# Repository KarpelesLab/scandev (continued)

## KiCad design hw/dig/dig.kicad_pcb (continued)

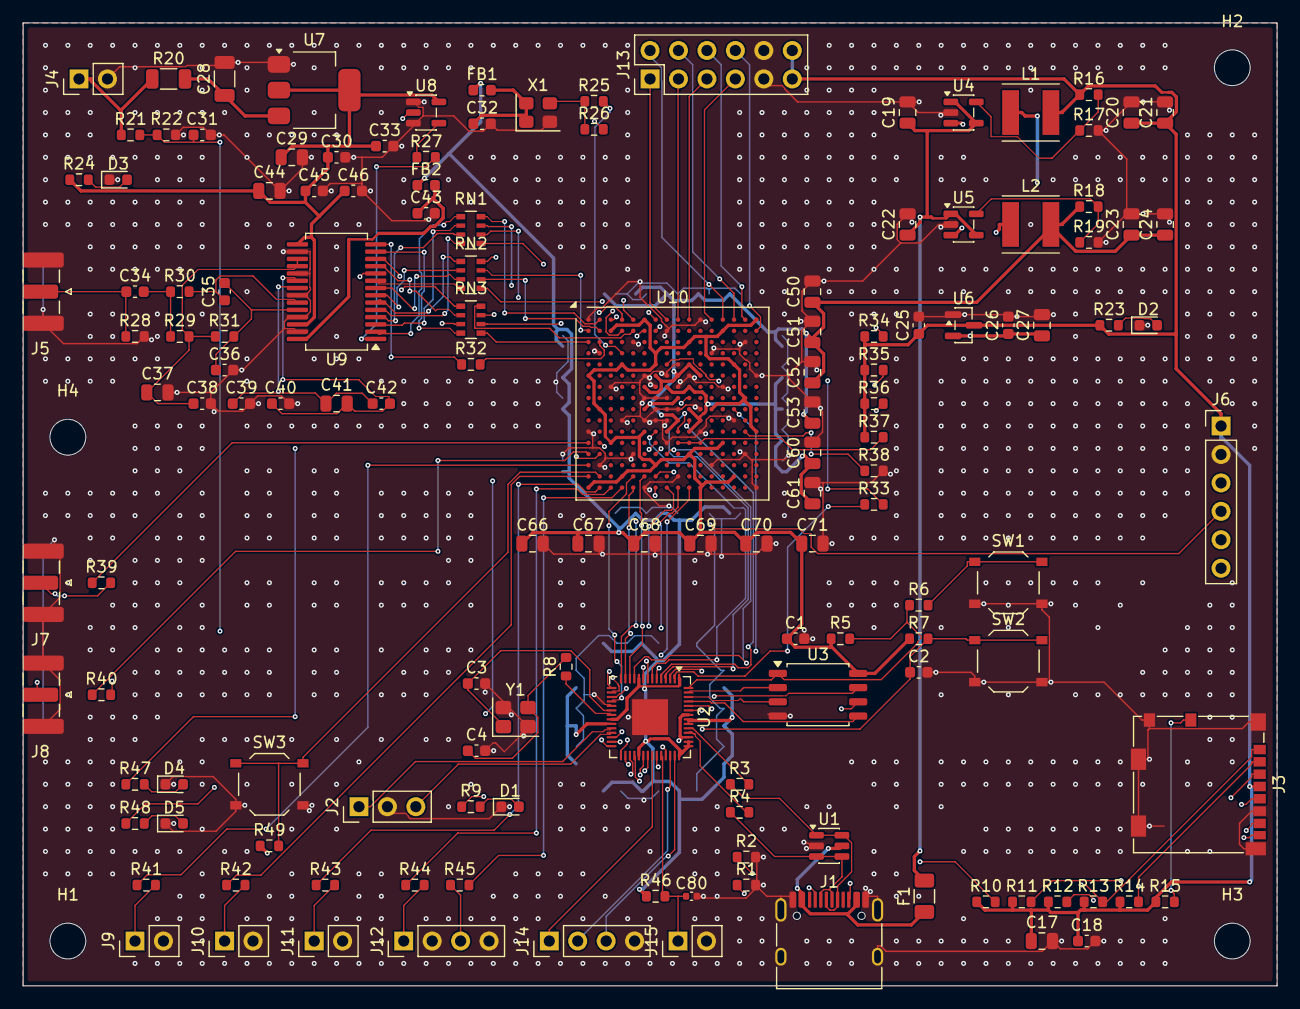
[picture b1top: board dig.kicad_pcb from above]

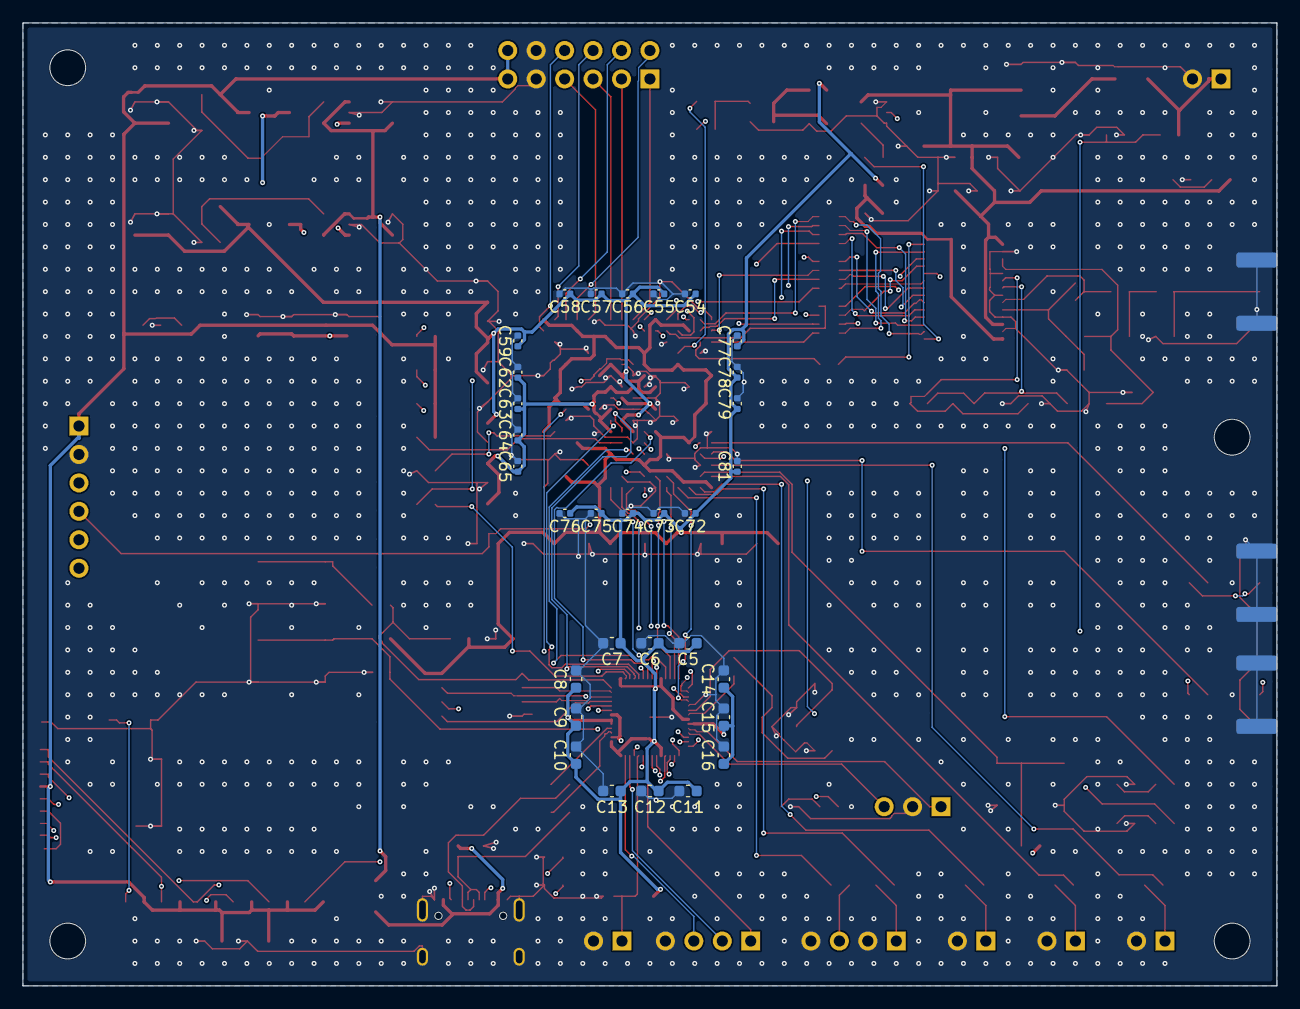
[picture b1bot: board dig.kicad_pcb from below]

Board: 4 copper layers, 112.0 x 86.0 mm, 174 parts (31 on the bottom side), 136 nets.

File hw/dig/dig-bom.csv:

Comment,Designator,Footprint,LCSC,MPN
100n,"C1,C10,C11,C12,C14,C15,C18,C2,C30,C31,C32,C33,C34,C36,C38,C39,C40,C42,C43,C45,C46,C5,C6,C7,C8,C9",C_0603_1608Metric,C14663,
1u,"C13,C16,C25,C26",C_0603_1608Metric,C15849,
10u,"C17,C19,C22,C27,C37,C41,C44",C_0805_2012Metric,C15850,
22u,"C20,C21,C23,C24,C29,C50,C51,C60,C66,C67",C_0805_2012Metric,C98190,
10u 25V,C28,C_1206_3216Metric,C9807,
15p,"C3,C4",C_0603_1608Metric,C107037,
22p,C35,C_0603_1608Metric,C525244,
4.7u,"C52,C53,C61,C68,C69,C70,C71",C_0805_2012Metric,C1779,
100n,"C54,C55,C56,C57,C58,C59,C62,C63,C64,C65,C72,C73,C74,C75,C76,C77,C78,C79,C80,C81",C_0402_1005Metric,C1525,
green,"D1,D2,D3,D4,D5",LED_0603_1608Metric,C72043,
1A hold,F1,Fuse_1206_3216Metric,C20800,SMD1206P100TF
600R,"FB1,FB2",L_0603_1608Metric,C1002,GZ1608D601TF
M3,"H1,H2,H3,H4",MountingHole_3.2mm_M3,,
USB-C,J1,USB_C_Receptacle_HRO_TYPE-C-31-M-12,C165948,TYPE-C-31-M-12
BLANK,J10,PinHeader_1x02_P2.54mm_Vertical,,
QDAMP,J11,PinHeader_1x02_P2.54mm_Vertical,,
TRIG,J12,PinHeader_1x04_P2.54mm_Vertical,,
PMOD,J13,PinHeader_2x06_P2.54mm_Vertical,,
EXP,J14,PinHeader_1x04_P2.54mm_Vertical,,
TEMP,J15,PinHeader_1x02_P2.54mm_Vertical,,
SWD,J2,PinHeader_1x03_P2.54mm_Vertical,,
microSD,J3,microSD_HC_Molex_104031-0811,C585350,104031-0811
12V IN,J4,PinHeader_1x02_P2.54mm_Vertical,,
RX IN,J5,SMA_Samtec_SMA-J-P-H-ST-EM1_EdgeMount,,
JTAG,J6,PinHeader_1x06_P2.54mm_Vertical,,
TX HI,J7,SMA_Samtec_SMA-J-P-H-ST-EM1_EdgeMount,,
TX LO,J8,SMA_Samtec_SMA-J-P-H-ST-EM1_EdgeMount,,
PA EN,J9,PinHeader_1x02_P2.54mm_Vertical,,
2.2u,"L1,L2",L_Changjiang_FNR5040S,C167957,FNR5040S2R2MT
5.1k,"R1,R2",R_0603_1608Metric,C2907044,
10k,"R10,R11,R12,R13,R14,R15,R46,R49,R5,R7",R_0603_1608Metric,C25804,
100k,"R16,R18,R21",R_0603_1608Metric,C115320,
22k,"R17,R22",R_0603_1608Metric,C114065,
150k,R19,R_0603_1608Metric,C402995,
10,R20,R_1206_3216Metric,C2828881,
1k,"R23,R29,R37,R38,R45,R47,R48,R6,R8,R9",R_0603_1608Metric,C21190,
2.2k,R24,R_0603_1608Metric,C844925,
33,"R25,R26,R27,R30,R31,R32,R33",R_0603_1608Metric,C23140,
49.9,"R28,R39,R40",R_0603_1608Metric,C23185,
27,"R3,R4",R_0603_1608Metric,C25190,
4.7k,"R34,R35,R36",R_0603_1608Metric,C116693,
100,"R41,R42,R43,R44",R_0603_1608Metric,C22775,
33,"RN1,RN2,RN3",R_Array_Convex_4x0603,C25508,4D03WGJ0330T5E
BOOTSEL,SW1,SW_Push_1P1T_XKB_TS-1187A,C318889,TS-1187A-C-C-B
RESET,SW2,SW_Push_1P1T_XKB_TS-1187A,C318889,TS-1187A-C-C-B
USER,SW3,SW_Push_1P1T_XKB_TS-1187A,C318889,TS-1187A-C-C-B
USBLC6-2SC6,U1,SOT-23-6,C7519,USBLC6-2SC6
XC7A35T-FTG256,U10,Xilinx_FTG256,C181716,XC7A35T-2FTG256C
RP2040,U2,QFN-56-1EP_7x7mm_P0.4mm_EP3.2x3.2mm,C2040,RP2040
W25Q16JV,U3,SOIC-8_5.3x5.3mm_P1.27mm,C131025,W25Q16JVSSIQ
TLV62569,"U4,U5",SOT-23-5,C141836,TLV62569DBVR
XC6206P182,U6,SOT-23,C51886219,XC6206P182MR
AMS1117-5.0,U7,SOT-223-3_TabPin2,C6187,AMS1117-5.0
74AHCT1G125,U8,SOT-23-5,C7484,SN74AHCT1G125DBVR
AD9226ARSZ,U9,SSOP-28_5.3x10.2mm_P0.65mm,C730053,AD9226ARSZ
50MHz,X1,Oscillator_SMD_Abracon_ASE-4Pin_3.2x2.5mm,C26267,SiT8008BI-22-33E-50.000000
12MHz,Y1,Crystal_SMD_3225-4Pin_3.2x2.5mm,C9002,X322512MSB4SI

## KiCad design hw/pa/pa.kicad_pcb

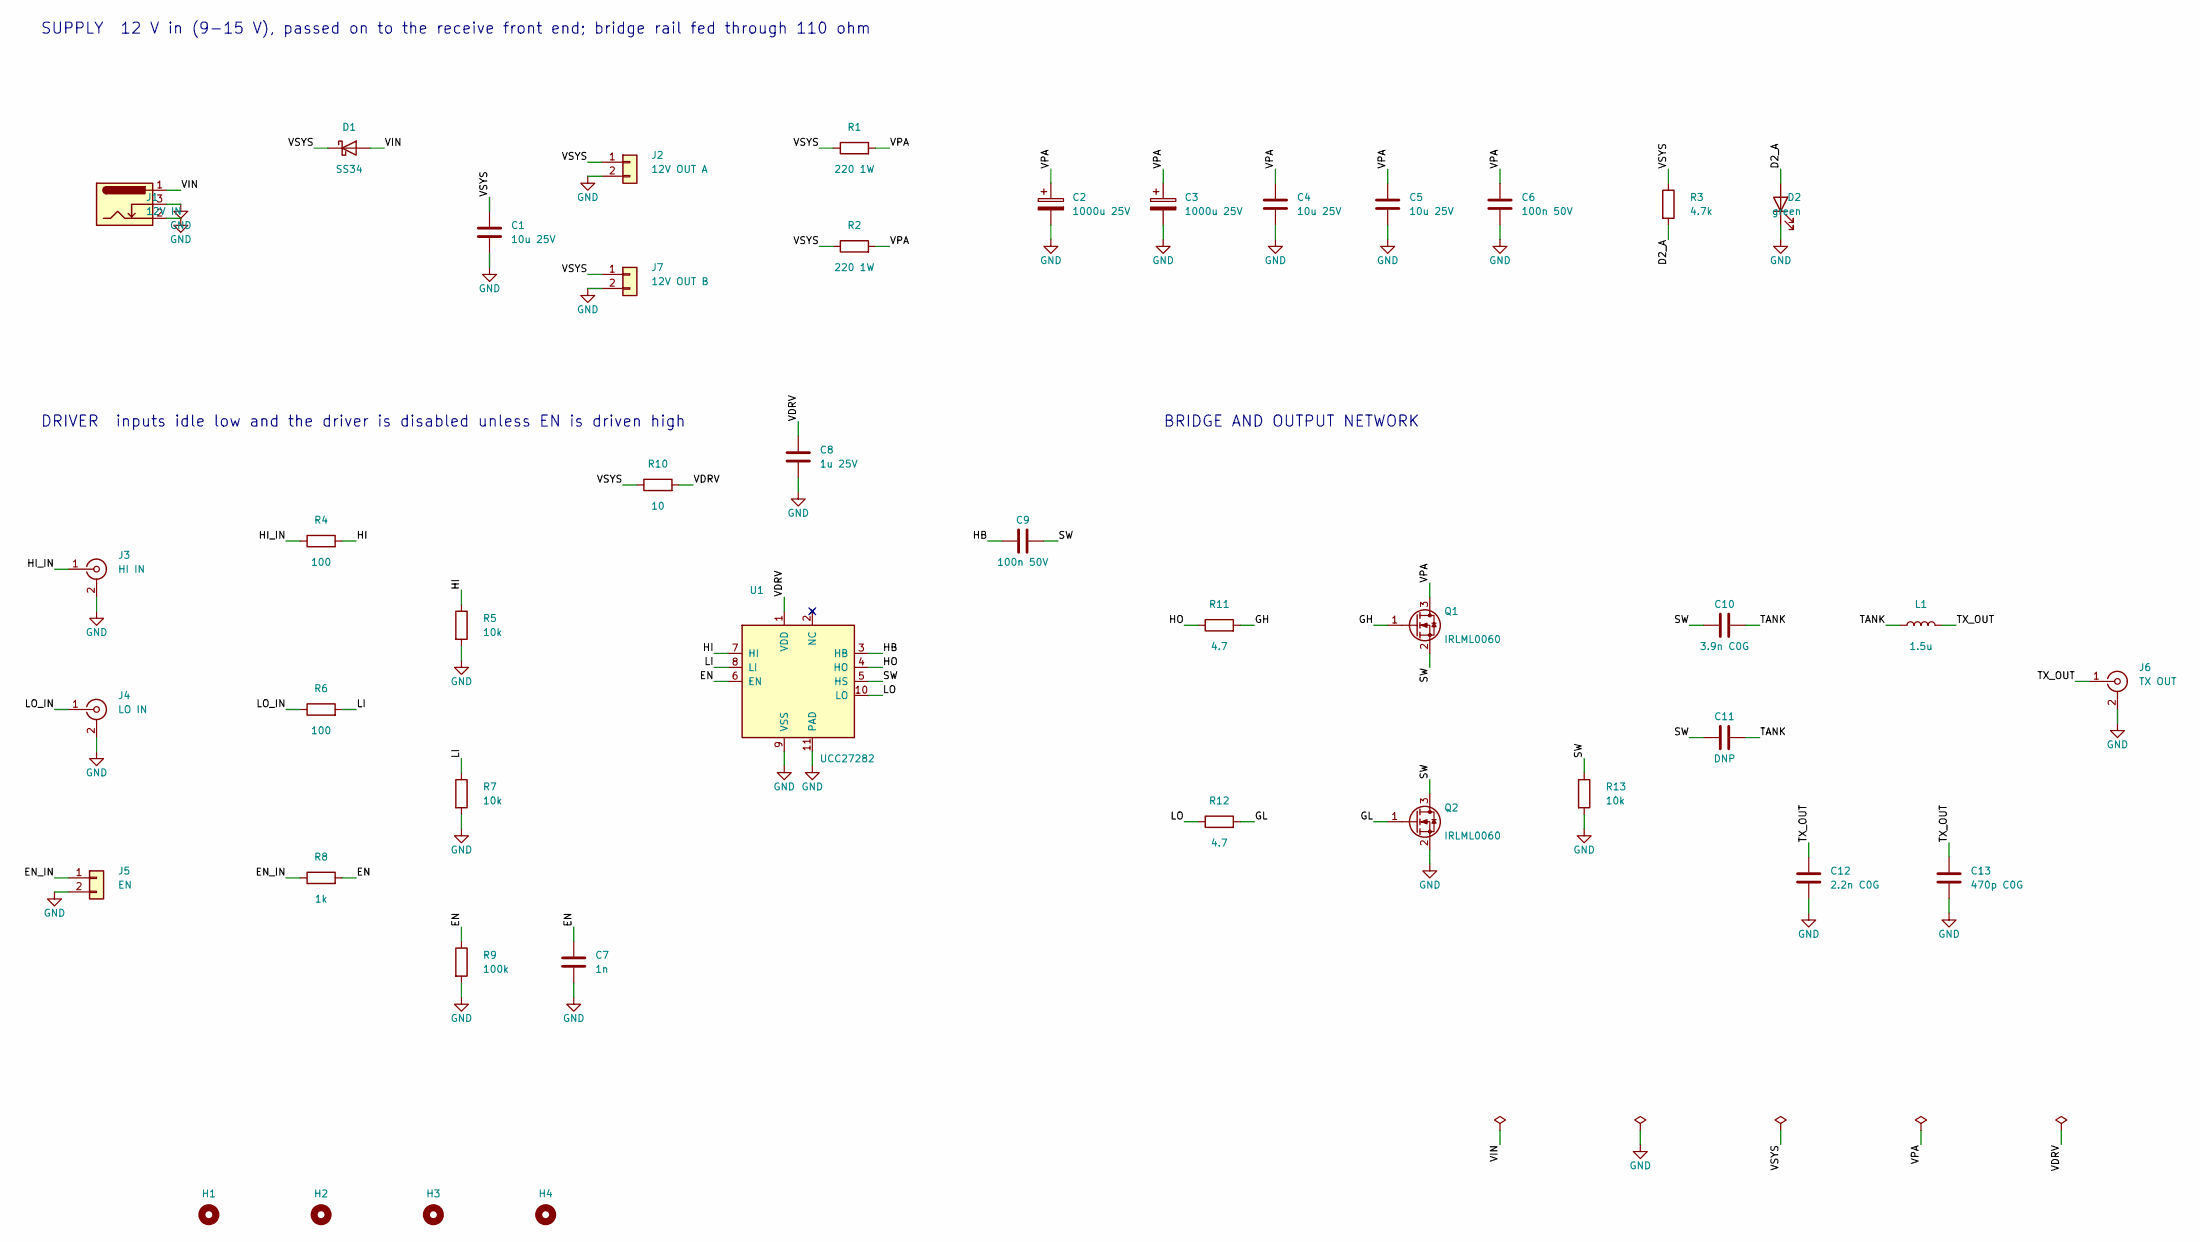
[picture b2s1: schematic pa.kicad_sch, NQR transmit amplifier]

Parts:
C1, C4, C5: 10u 25V; C_1206_3216Metric; LCSC C9807
C2, C3: 1000u 25V; CP_Radial_D10.0mm_P5.00mm; MPN 25YXJ1000M10X20; LCSC C88720
C6, C9: 100n 50V; C_0603_1608Metric; LCSC C88219
C7: 1n; C_0603_1608Metric; LCSC C106247
C8: 1u 25V; C_0603_1608Metric; LCSC C92848
C10: 3.9n C0G; C_0805_2012Metric; LCSC C97901
C11: DNP; C_0805_2012Metric
C12: 2.2n C0G; C_0805_2012Metric; LCSC C513663
C13: 470p C0G; C_0805_2012Metric; LCSC C575439
D1: SS34; D_SMA; MPN SS34; LCSC C8678
D2: green; LED_0603_1608Metric; LCSC C72043
H1, H2, H3, H4: M3; MountingHole_3.2mm_M3
J1: 12V IN; BarrelJack_Horizontal; MPN DC005-T; LCSC C431532
J2: 12V OUT A; PinHeader_1x02_P2.54mm_Vertical
J3: HI IN; SMA_Samtec_SMA-J-P-H-ST-EM1_EdgeMount
J4: LO IN; SMA_Samtec_SMA-J-P-H-ST-EM1_EdgeMount
J5: EN; PinHeader_1x02_P2.54mm_Vertical
J6: TX OUT; SMA_Samtec_SMA-J-P-H-ST-EM1_EdgeMount
J7: 12V OUT B; PinHeader_1x02_P2.54mm_Vertical
L1: 1.5u; L_Sunlord_MWSA0503S; MPN MWSA0503S-1R5MT; LCSC C408407
Q1, Q2: IRLML0060; SOT-23; MPN IRLML0060TRPBF; LCSC C5122025
R1, R2: 220 1W; R_2512_6332Metric; LCSC C38808
R3: 4.7k; R_0603_1608Metric; LCSC C116693
R4, R6: 100; R_0603_1608Metric; LCSC C22775
R5, R7, R13: 10k; R_0603_1608Metric; LCSC C25804
R8: 1k; R_0603_1608Metric; LCSC C21190
R9: 100k; R_0603_1608Metric; LCSC C115320
R10: 10; R_0603_1608Metric; LCSC C22859
R11, R12: 4.7; R_0603_1608Metric; LCSC C844794
U1: UCC27282; Texas_DRC0010J; MPN UCC27282DRCR; LCSC C2677035

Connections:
D2_A: D2.2 (A), R3.2
EN: C7.1, R8.2, R9.1, U1.6 (EN)
EN_IN: J5.1, R8.1
GH: Q1.1 (G), R11.2
GL: Q2.1 (G), R12.2
GND: C1.2, C2.2, C3.2, C4.2, C5.2, C6.2, C7.2, C8.2, C12.2, C13.2, D2.1 (K), J1.2, J1.3, J2.2, J3.2 (Ext), J4.2 (Ext), J5.2, J6.2 (Ext), J7.2, Q2.2 (S), R5.2, R7.2, R9.2, R13.2, U1.9 (VSS), U1.11 (PAD)
HB: C9.1, U1.3 (HB)
HI: R4.2, R5.1, U1.7 (HI)
HI_IN: J3.1 (In), R4.1
HO: R11.1, U1.4 (HO)
LI: R6.2, R7.1, U1.8 (LI)
LO: R12.1, U1.10 (LO)
LO_IN: J4.1 (In), R6.1
SW: C9.2, C10.1, C11.1, Q1.2 (S), Q2.3 (D), R13.1, U1.5 (HS)
TANK: C10.2, C11.2, L1.1
TX_OUT: C12.1, C13.1, J6.1 (In), L1.2
VDRV: C8.1, R10.2, U1.1 (VDD)
VIN: D1.2 (A), J1.1
VPA: C2.1, C3.1, C4.1, C5.1, C6.1, Q1.3 (D), R1.2, R2.2
VSYS: C1.1, D1.1 (K), J2.1, J7.1, R1.1, R2.1, R3.1, R10.1

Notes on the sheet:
SUPPLY 12 V in (9-15 V), passed on to the receive front end; bridge rail fed through 110 ohm
DRIVER inputs idle low and the driver is disabled unless EN is driven high
BRIDGE AND OUTPUT NETWORK

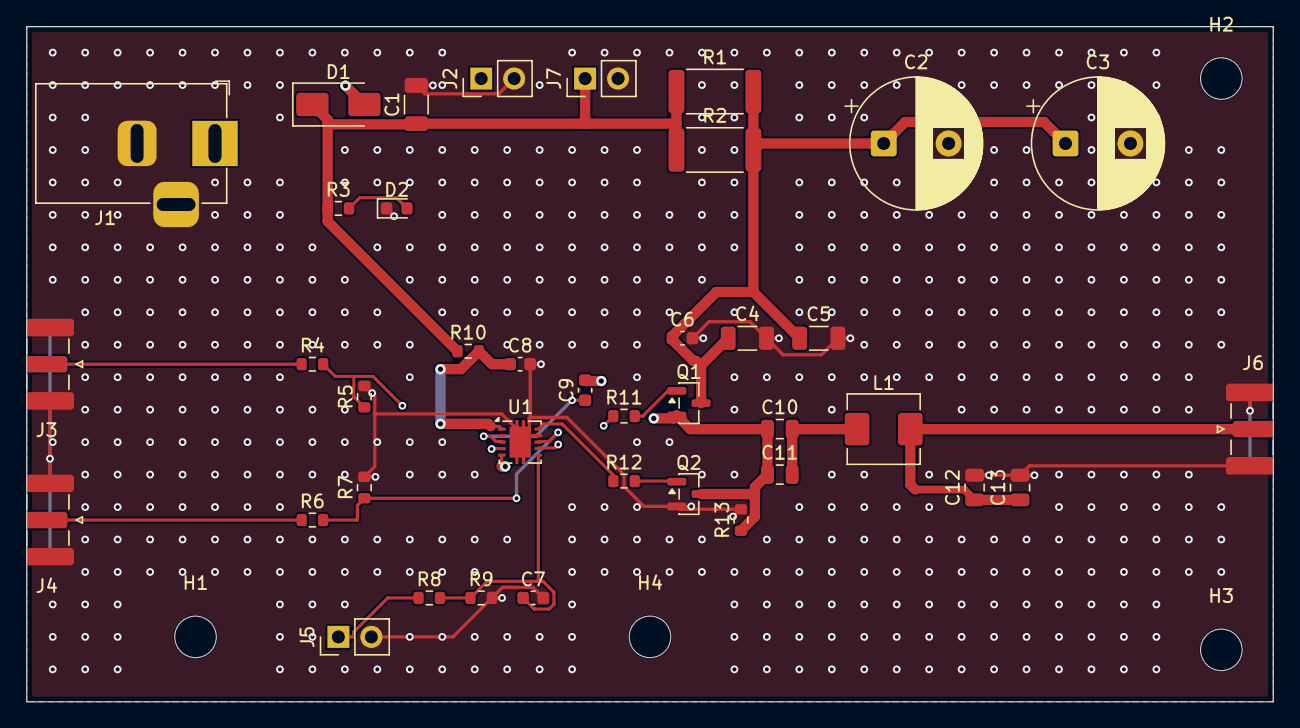
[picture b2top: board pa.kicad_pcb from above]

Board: 4 copper layers, 96.0 x 52.0 mm, 43 parts (0 on the bottom side), 20 nets.

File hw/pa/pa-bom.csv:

Comment,Designator,Footprint,LCSC,MPN
10u 25V,"C1,C4,C5",C_1206_3216Metric,C9807,
3.9n C0G,C10,C_0805_2012Metric,C97901,
DNP,C11,C_0805_2012Metric,,
2.2n C0G,C12,C_0805_2012Metric,C513663,
470p C0G,C13,C_0805_2012Metric,C575439,
1000u 25V,"C2,C3",CP_Radial_D10.0mm_P5.00mm,C88720,25YXJ1000M10X20
100n 50V,"C6,C9",C_0603_1608Metric,C88219,
1n,C7,C_0603_1608Metric,C106247,
1u 25V,C8,C_0603_1608Metric,C92848,
SS34,D1,D_SMA,C8678,SS34
green,D2,LED_0603_1608Metric,C72043,
M3,"H1,H2,H3,H4",MountingHole_3.2mm_M3,,
12V IN,J1,BarrelJack_Horizontal,C431532,DC005-T
12V OUT A,J2,PinHeader_1x02_P2.54mm_Vertical,,
HI IN,J3,SMA_Samtec_SMA-J-P-H-ST-EM1_EdgeMount,,
LO IN,J4,SMA_Samtec_SMA-J-P-H-ST-EM1_EdgeMount,,
EN,J5,PinHeader_1x02_P2.54mm_Vertical,,
TX OUT,J6,SMA_Samtec_SMA-J-P-H-ST-EM1_EdgeMount,,
12V OUT B,J7,PinHeader_1x02_P2.54mm_Vertical,,
1.5u,L1,L_Sunlord_MWSA0503S,C408407,MWSA0503S-1R5MT
IRLML0060,"Q1,Q2",SOT-23,C5122025,IRLML0060TRPBF
220 1W,"R1,R2",R_2512_6332Metric,C38808,
10,R10,R_0603_1608Metric,C22859,
4.7,"R11,R12",R_0603_1608Metric,C844794,
10k,"R13,R5,R7",R_0603_1608Metric,C25804,
4.7k,R3,R_0603_1608Metric,C116693,
100,"R4,R6",R_0603_1608Metric,C22775,
1k,R8,R_0603_1608Metric,C21190,
100k,R9,R_0603_1608Metric,C115320,
UCC27282,U1,Texas_DRC0010J,C2677035,UCC27282DRCR

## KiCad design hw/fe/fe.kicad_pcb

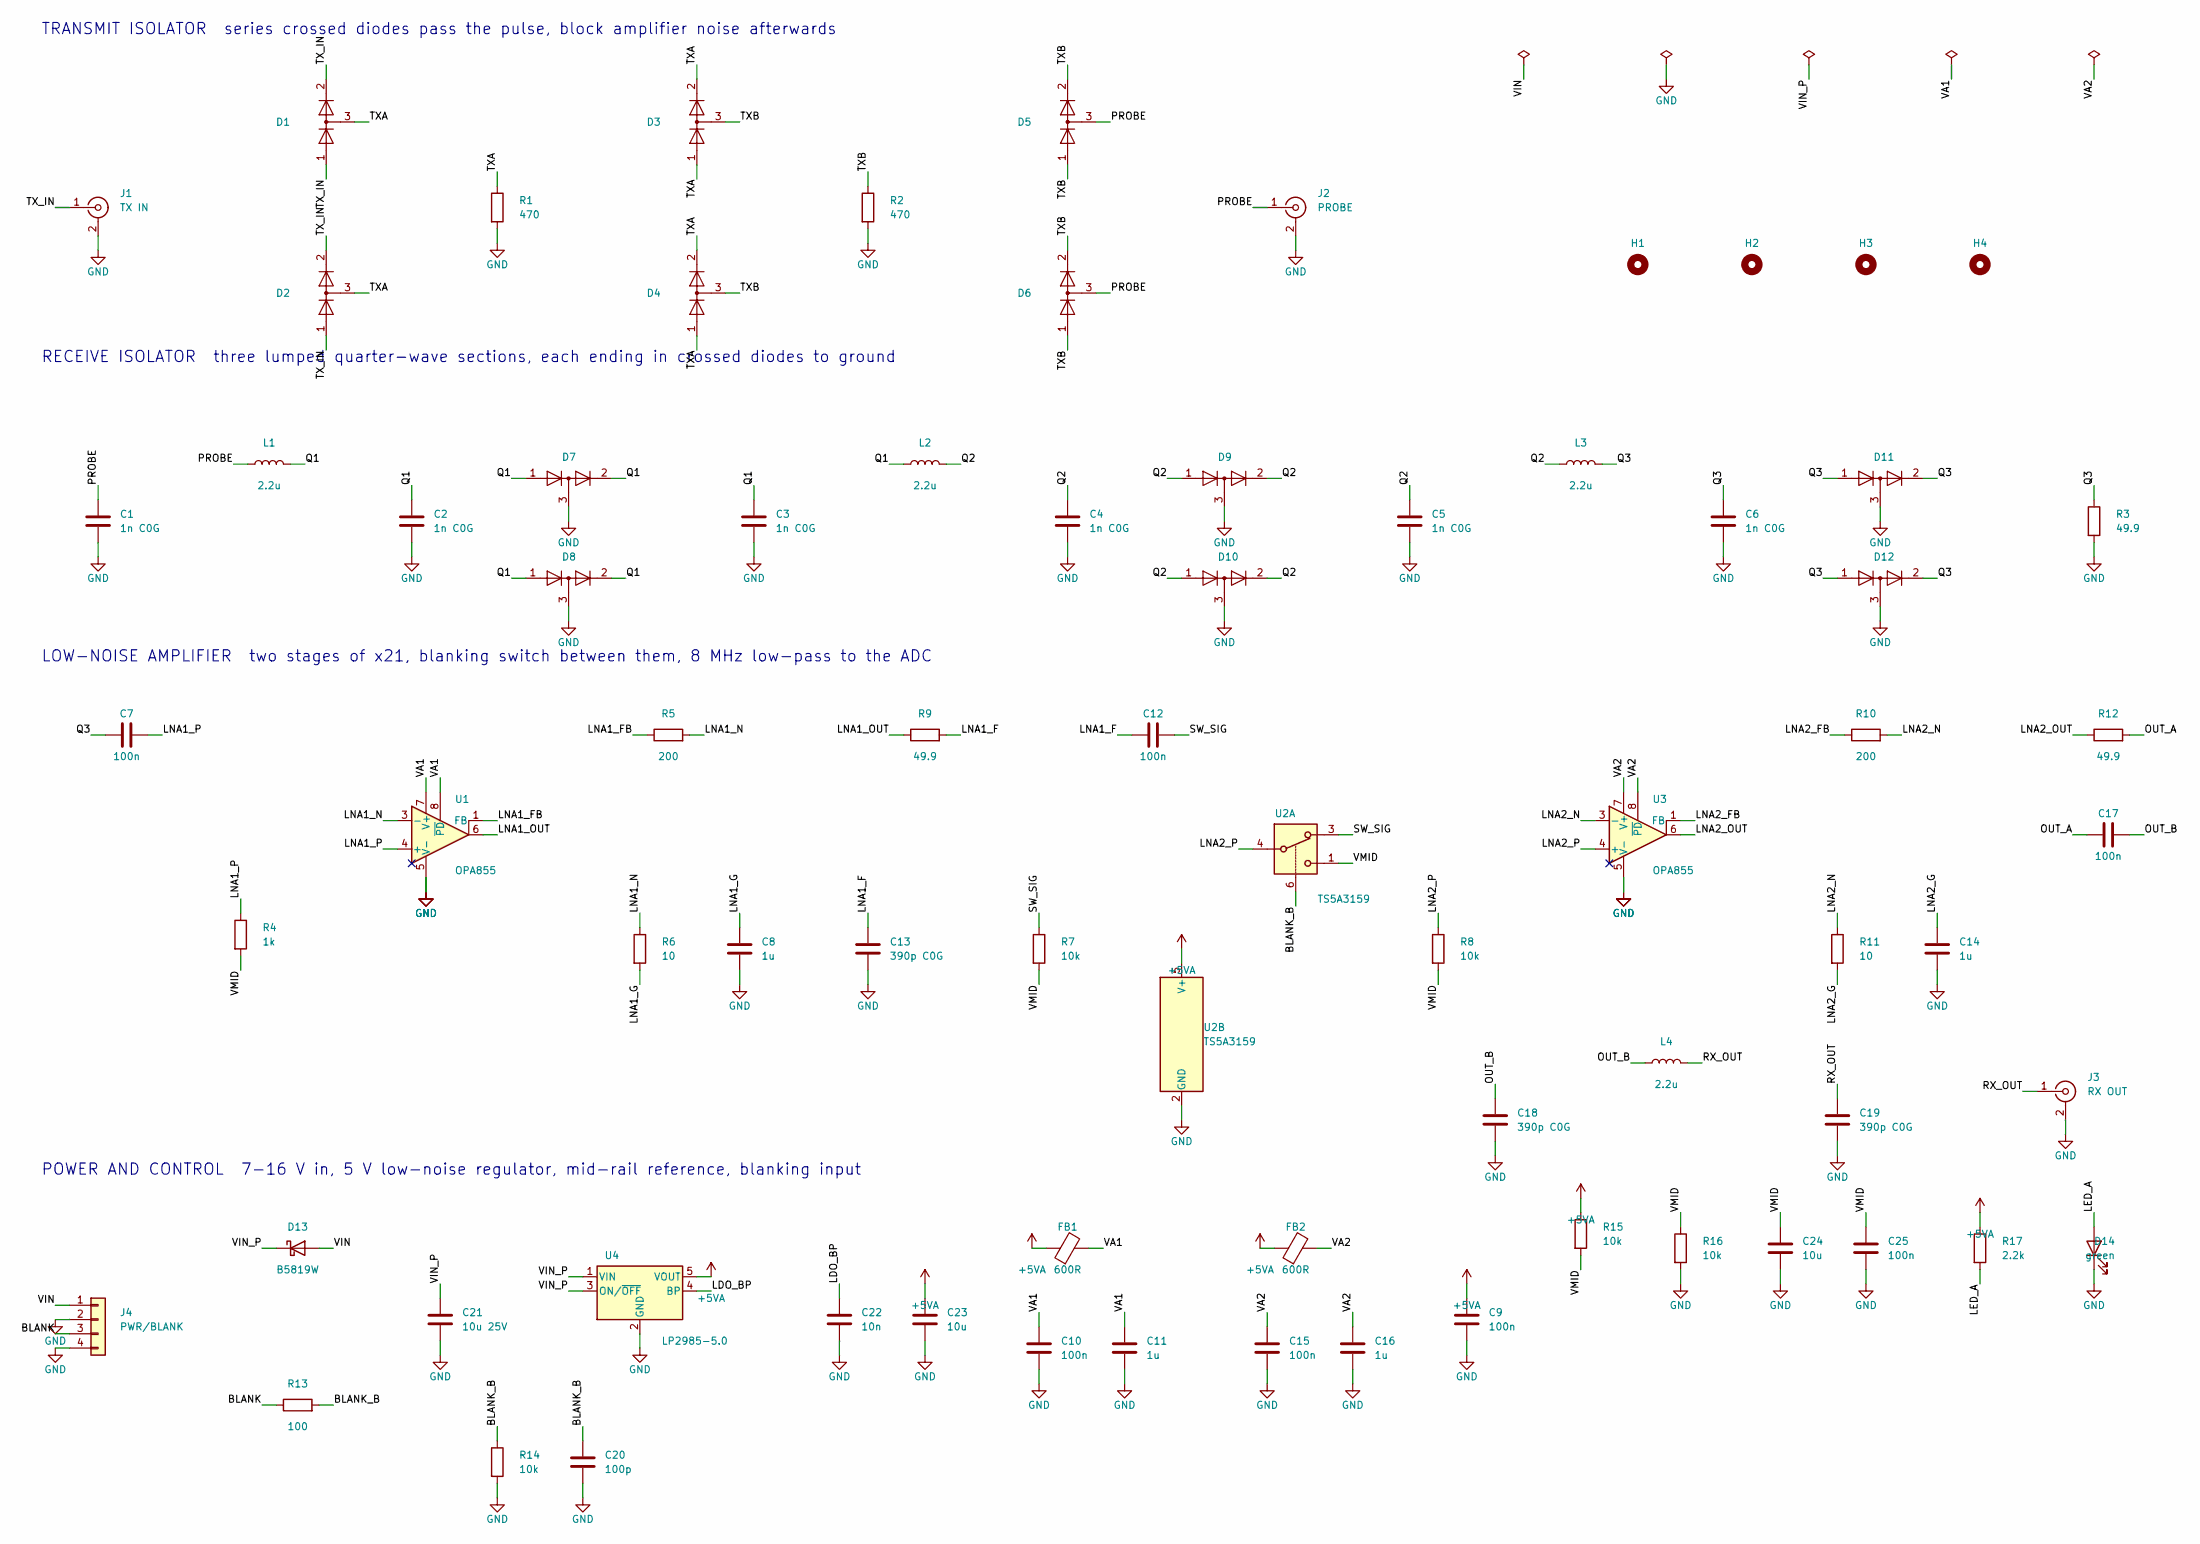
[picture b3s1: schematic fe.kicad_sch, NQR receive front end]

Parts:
C1, C2, C3, C4, C5, C6: 1n C0G; C_0805_2012Metric; LCSC C62774
C7, C9, C10, C12, C15, C17, C25: 100n; C_0603_1608Metric; LCSC C14663
C8, C11, C14, C16: 1u; C_0603_1608Metric; LCSC C15849
C13, C18, C19: 390p C0G; C_0603_1608Metric; LCSC C1667
C20: 100p; C_0603_1608Metric; LCSC C14858
C21: 10u 25V; C_0805_2012Metric; LCSC C84416
C22: 10n; C_0603_1608Metric; LCSC C57112
C23, C24: 10u; C_0805_2012Metric; LCSC C15850
D1, D2, D3, D4, D5, D6, D7, D8, D9, D10, D11, D12: BAV99; SOT-23; MPN BAV99LT1G; LCSC C82480
D13: B5819W; D_SOD-123; MPN B5819W; LCSC C8598
D14: green; LED_0603_1608Metric; LCSC C72043
FB1, FB2: 600R; L_0603_1608Metric; MPN GZ1608D601TF; LCSC C1002
H1, H2, H3, H4: M3; MountingHole_3.2mm_M3
J1: TX IN; SMA_Samtec_SMA-J-P-H-ST-EM1_EdgeMount
J2: PROBE; SMA_Samtec_SMA-J-P-H-ST-EM1_EdgeMount
J3: RX OUT; SMA_Samtec_SMA-J-P-H-ST-EM1_EdgeMount
J4: PWR/BLANK; PinHeader_1x04_P2.54mm_Vertical
L1, L2, L3, L4: 2.2u; L_Changjiang_FNR5040S; MPN FNR5040S2R2MT; LCSC C167957
R1, R2: 470; R_1206_3216Metric; LCSC C4502
R3, R9, R12: 49.9; R_0603_1608Metric; LCSC C23185
R4: 1k; R_0603_1608Metric; LCSC C21190
R5, R10: 200; R_0603_1608Metric; LCSC C8218
R6, R11: 10; R_0603_1608Metric; LCSC C22859
R7, R8, R14, R15, R16: 10k; R_0603_1608Metric; LCSC C25804
R13: 100; R_0603_1608Metric; LCSC C22775
R17: 2.2k; R_0603_1608Metric; LCSC C844925
U1, U3: OPA855; Texas_DSG0008A_WSON-8-1EP_2x2mm_P0.5mm_EP0.9x1.6mm; MPN OPA855IDSGR; LCSC C1409030
U2: TS5A3159; SOT-363_SC-70-6; MPN TS5A3159DCKR; LCSC C46388
U4: LP2985-5.0; SOT-23-5; MPN LP2985-50DBVR; LCSC C74511

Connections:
+5VA: C9.1, C23.1, FB1.1, FB2.1, R15.1, R17.1, U2.5 (V+), U4.5 (VOUT)
BLANK: J4.3, R13.1
BLANK_B: C20.1, R13.2, R14.1, U2.6
GND: C1.2, C2.2, C3.2, C4.2, C5.2, C6.2, C8.2, C9.2, C10.2, C11.2, C13.2, C14.2, C15.2, C16.2, C18.2, C19.2, C20.2, C21.2, C22.2, C23.2, C24.2, C25.2, D7.3 (K), D8.3 (K), D9.3 (K), D10.3 (K), D11.3 (K), D12.3 (K), D14.1 (K), J1.2 (Ext), J2.2 (Ext), J3.2 (Ext), J4.2, J4.4, R1.2, R2.2, R3.2, R14.2, R16.2, U1.5 (V-), U1.9 (V-), U2.2 (GND), U3.5 (V-), U3.9 (V-), U4.2 (GND)
LDO_BP: C22.1, U4.4 (BP)
LED_A: D14.2 (A), R17.2
LNA1_F: C12.1, C13.1, R9.2
LNA1_FB: R5.1, U1.1 (FB)
LNA1_G: C8.1, R6.2
LNA1_N: R5.2, R6.1, U1.3 (-)
LNA1_OUT: R9.1, U1.6
LNA1_P: C7.2, R4.1, U1.4 (+)
LNA2_FB: R10.1, U3.1 (FB)
LNA2_G: C14.1, R11.2
LNA2_N: R10.2, R11.1, U3.3 (-)
LNA2_OUT: R12.1, U3.6
LNA2_P: R8.1, U2.4, U3.4 (+)
OUT_A: C17.1, R12.2
OUT_B: C17.2, C18.1, L4.1
PROBE: C1.1, D5.3 (K), D6.3 (K), J2.1 (In), L1.1
Q1: C2.1, C3.1, D7.1 (K), D7.2 (A), D8.1 (K), D8.2 (A), L1.2, L2.1
Q2: C4.1, C5.1, D9.1 (K), D9.2 (A), D10.1 (K), D10.2 (A), L2.2, L3.1
Q3: C6.1, C7.1, D11.1 (K), D11.2 (A), D12.1 (K), D12.2 (A), L3.2, R3.1
RX_OUT: C19.1, J3.1 (In), L4.2
SW_SIG: C12.2, R7.1, U2.3
TXA: D1.3 (K), D2.3 (K), D3.1 (K), D3.2 (A), D4.1 (K), D4.2 (A), R1.1
TXB: D3.3 (K), D4.3 (K), D5.1 (K), D5.2 (A), D6.1 (K), D6.2 (A), R2.1
TX_IN: D1.1 (K), D1.2 (A), D2.1 (K), D2.2 (A), J1.1 (In)
VA1: C10.1, C11.1, FB1.2, U1.7 (V+), U1.8 (~PD)
VA2: C15.1, C16.1, FB2.2, U3.7 (V+), U3.8 (~PD)
VIN: D13.2 (A), J4.1
VIN_P: C21.1, D13.1 (K), U4.1 (VIN), U4.3 (ON/~OFF)
VMID: C24.1, C25.1, R4.2, R7.2, R8.2, R15.2, R16.1, U2.1

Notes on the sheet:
TRANSMIT ISOLATOR series crossed diodes pass the pulse, block amplifier noise afterwards
RECEIVE ISOLATOR three lumped quarter-wave sections, each ending in crossed diodes to ground
LOW-NOISE AMPLIFIER two stages of x21, blanking switch between them, 8 MHz low-pass to the ADC
POWER AND CONTROL 7-16 V in, 5 V low-noise regulator, mid-rail reference, blanking input

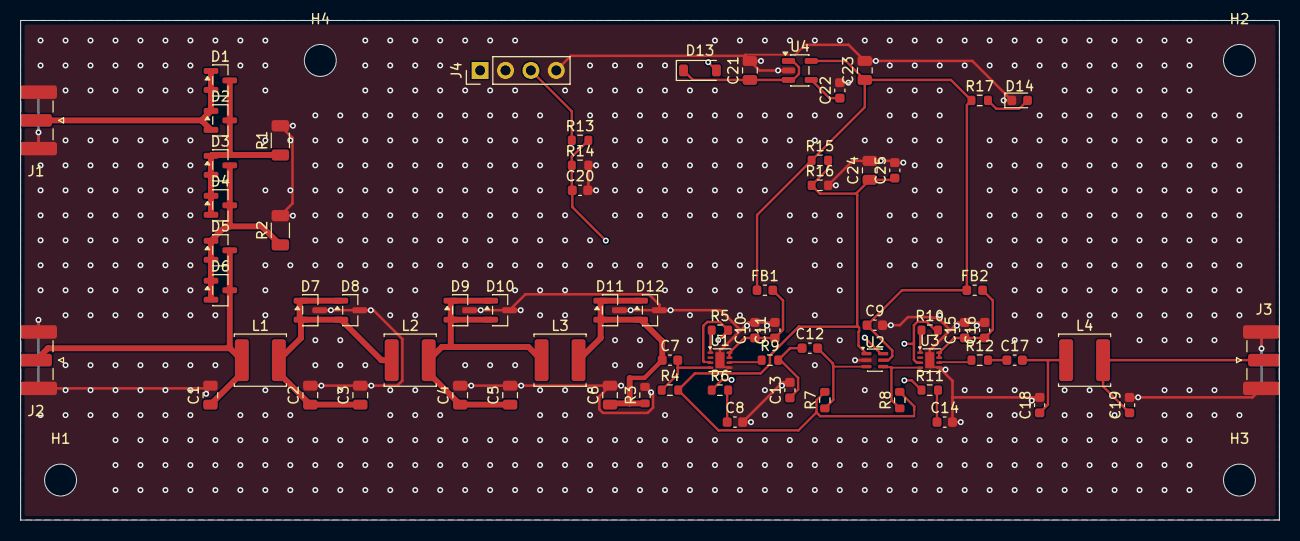
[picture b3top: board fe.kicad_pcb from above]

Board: 4 copper layers, 126.0 x 50.0 mm, 74 parts (0 on the bottom side), 33 nets.

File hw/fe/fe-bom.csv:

Comment,Designator,Footprint,LCSC,MPN
1n C0G,"C1,C2,C3,C4,C5,C6",C_0805_2012Metric,C62774,
100n,"C10,C12,C15,C17,C25,C7,C9",C_0603_1608Metric,C14663,
1u,"C11,C14,C16,C8",C_0603_1608Metric,C15849,
390p C0G,"C13,C18,C19",C_0603_1608Metric,C1667,
100p,C20,C_0603_1608Metric,C14858,
10u 25V,C21,C_0805_2012Metric,C84416,
10n,C22,C_0603_1608Metric,C57112,
10u,"C23,C24",C_0805_2012Metric,C15850,
BAV99,"D1,D10,D11,D12,D2,D3,D4,D5,D6,D7,D8,D9",SOT-23,C82480,BAV99LT1G
B5819W,D13,D_SOD-123,C8598,B5819W
green,D14,LED_0603_1608Metric,C72043,
600R,"FB1,FB2",L_0603_1608Metric,C1002,GZ1608D601TF
M3,"H1,H2,H3,H4",MountingHole_3.2mm_M3,,
TX IN,J1,SMA_Samtec_SMA-J-P-H-ST-EM1_EdgeMount,,
PROBE,J2,SMA_Samtec_SMA-J-P-H-ST-EM1_EdgeMount,,
RX OUT,J3,SMA_Samtec_SMA-J-P-H-ST-EM1_EdgeMount,,
PWR/BLANK,J4,PinHeader_1x04_P2.54mm_Vertical,,
2.2u,"L1,L2,L3,L4",L_Changjiang_FNR5040S,C167957,FNR5040S2R2MT
470,"R1,R2",R_1206_3216Metric,C4502,
200,"R10,R5",R_0603_1608Metric,C8218,
10,"R11,R6",R_0603_1608Metric,C22859,
49.9,"R12,R3,R9",R_0603_1608Metric,C23185,
100,R13,R_0603_1608Metric,C22775,
10k,"R14,R15,R16,R7,R8",R_0603_1608Metric,C25804,
2.2k,R17,R_0603_1608Metric,C844925,
1k,R4,R_0603_1608Metric,C21190,
OPA855,"U1,U3",Texas_DSG0008A_WSON-8-1EP_2x2mm_P0.5mm_EP0.9x1.6mm,C1409030,OPA855IDSGR
TS5A3159,U2,SOT-363_SC-70-6,C46388,TS5A3159DCKR
LP2985-5.0,U4,SOT-23-5,C74511,LP2985-50DBVR

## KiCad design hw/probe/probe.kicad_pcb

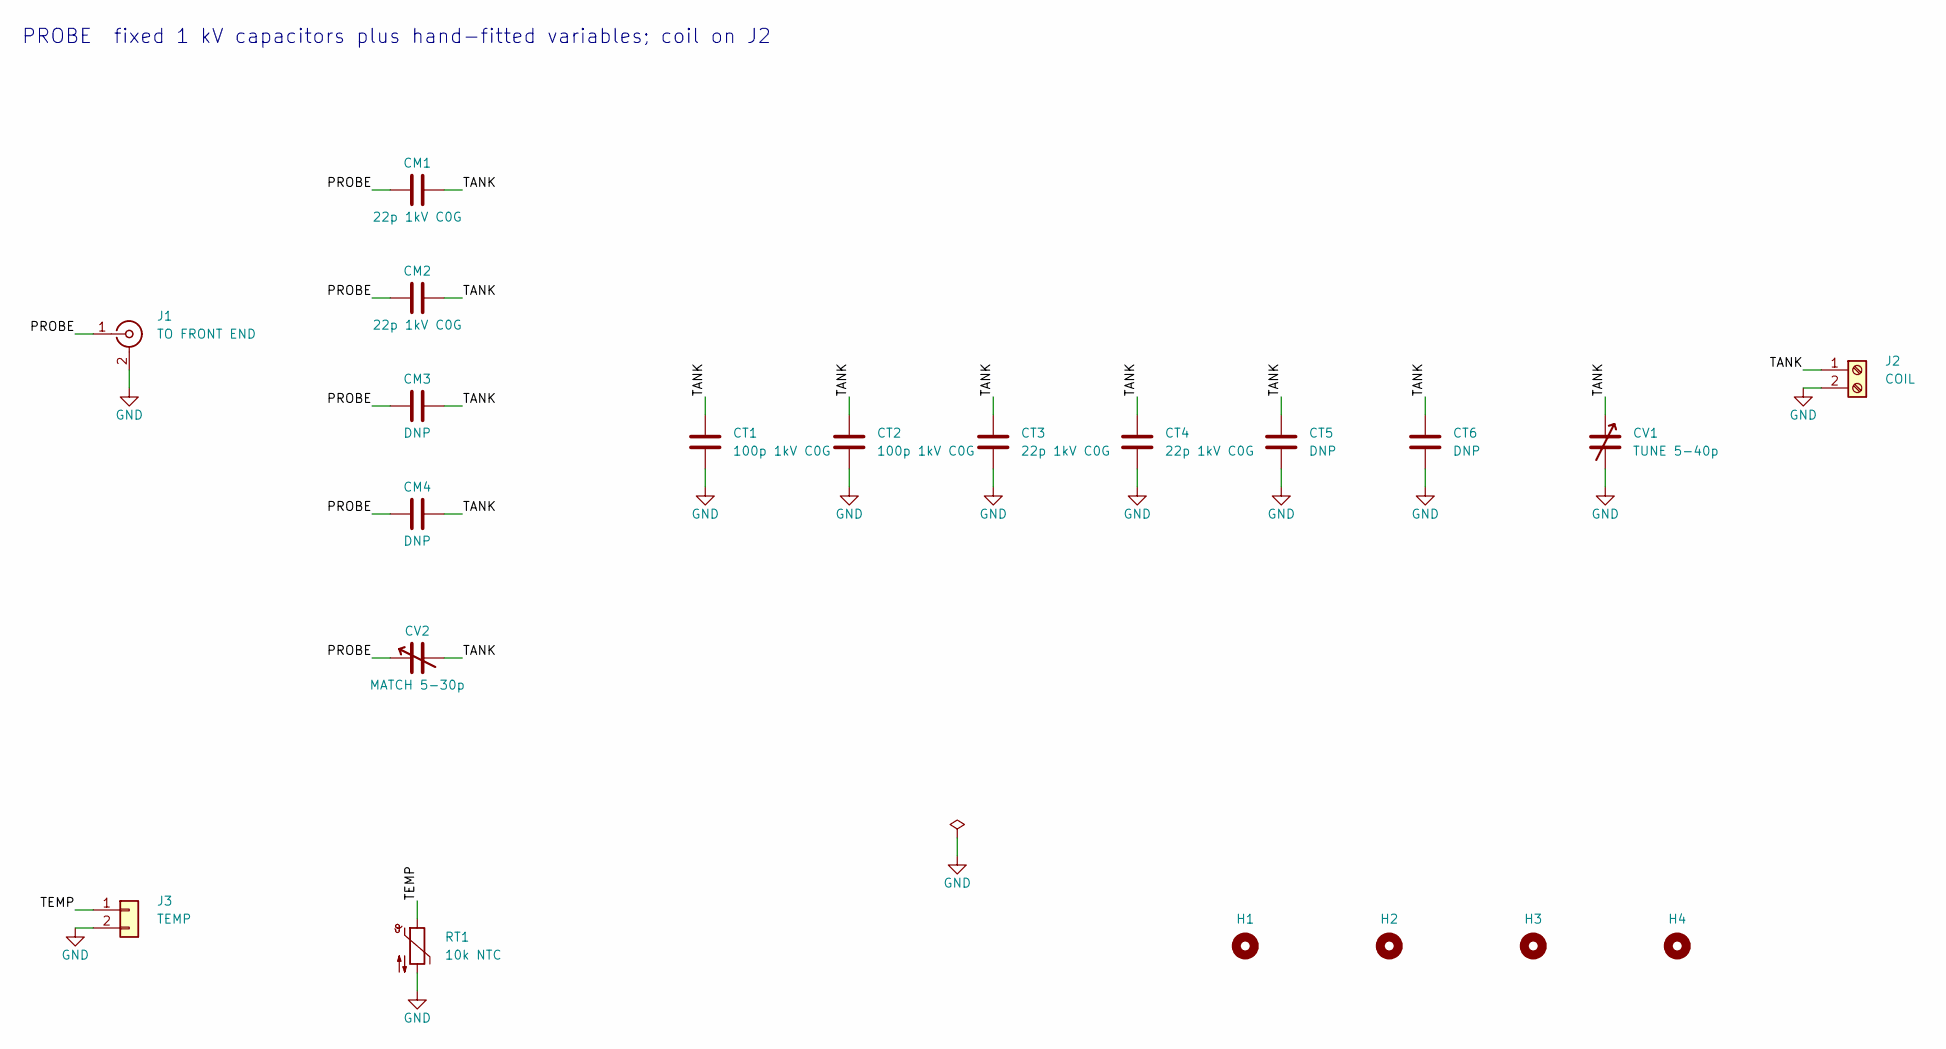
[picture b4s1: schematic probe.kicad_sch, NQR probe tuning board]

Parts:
CM1, CM2: 22p 1kV C0G; C_1206_3216Metric; LCSC C107174
CM3, CM4: DNP; C_1206_3216Metric
CT1, CT2: 100p 1kV C0G; C_1206_3216Metric; LCSC C9188
CT3, CT4: 22p 1kV C0G; C_1206_3216Metric; LCSC C107174
CT5, CT6: DNP; C_1206_3216Metric
CV1: TUNE 5-40p; SolderWire-0.75sqmm_1x02_P7mm_D1.25mm_OD3.5mm; MPN variable capacitor, >=500 V
CV2: MATCH 5-30p; SolderWire-0.75sqmm_1x02_P7mm_D1.25mm_OD3.5mm; MPN variable capacitor, >=500 V
H1, H2, H3, H4: M3; MountingHole_3.2mm_M3
J1: TO FRONT END; SMA_Samtec_SMA-J-P-H-ST-EM1_EdgeMount
J2: COIL; TerminalBlock_Phoenix_MKDS-1,5-2_1x02_P5.00mm_Horizontal
J3: TEMP; PinHeader_1x02_P2.54mm_Vertical
RT1: 10k NTC; R_0603_1608Metric; MPN 10k B3950 NTC 0603

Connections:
GND: CT1.2, CT2.2, CT3.2, CT4.2, CT5.2, CT6.2, CV1.2, J1.2 (Ext), J2.2, J3.2, RT1.2
PROBE: CM1.1, CM2.1, CM3.1, CM4.1, CV2.1, J1.1 (In)
TANK: CM1.2, CM2.2, CM3.2, CM4.2, CT1.1, CT2.1, CT3.1, CT4.1, CT5.1, CT6.1, CV1.1, CV2.2, J2.1
TEMP: J3.1, RT1.1

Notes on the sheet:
PROBE fixed 1 kV capacitors plus hand-fitted variables; coil on J2

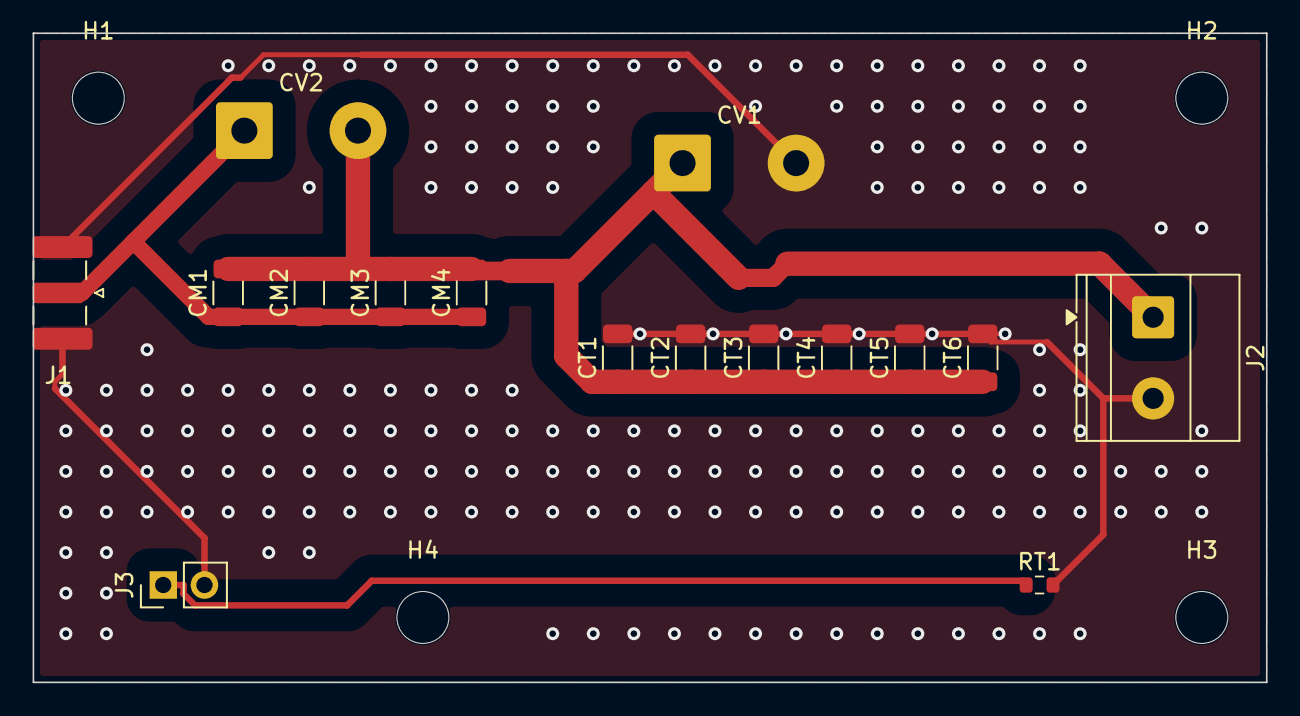
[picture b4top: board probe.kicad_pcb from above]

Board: 2 copper layers, 76.0 x 40.0 mm, 20 parts (0 on the bottom side), 4 nets.
